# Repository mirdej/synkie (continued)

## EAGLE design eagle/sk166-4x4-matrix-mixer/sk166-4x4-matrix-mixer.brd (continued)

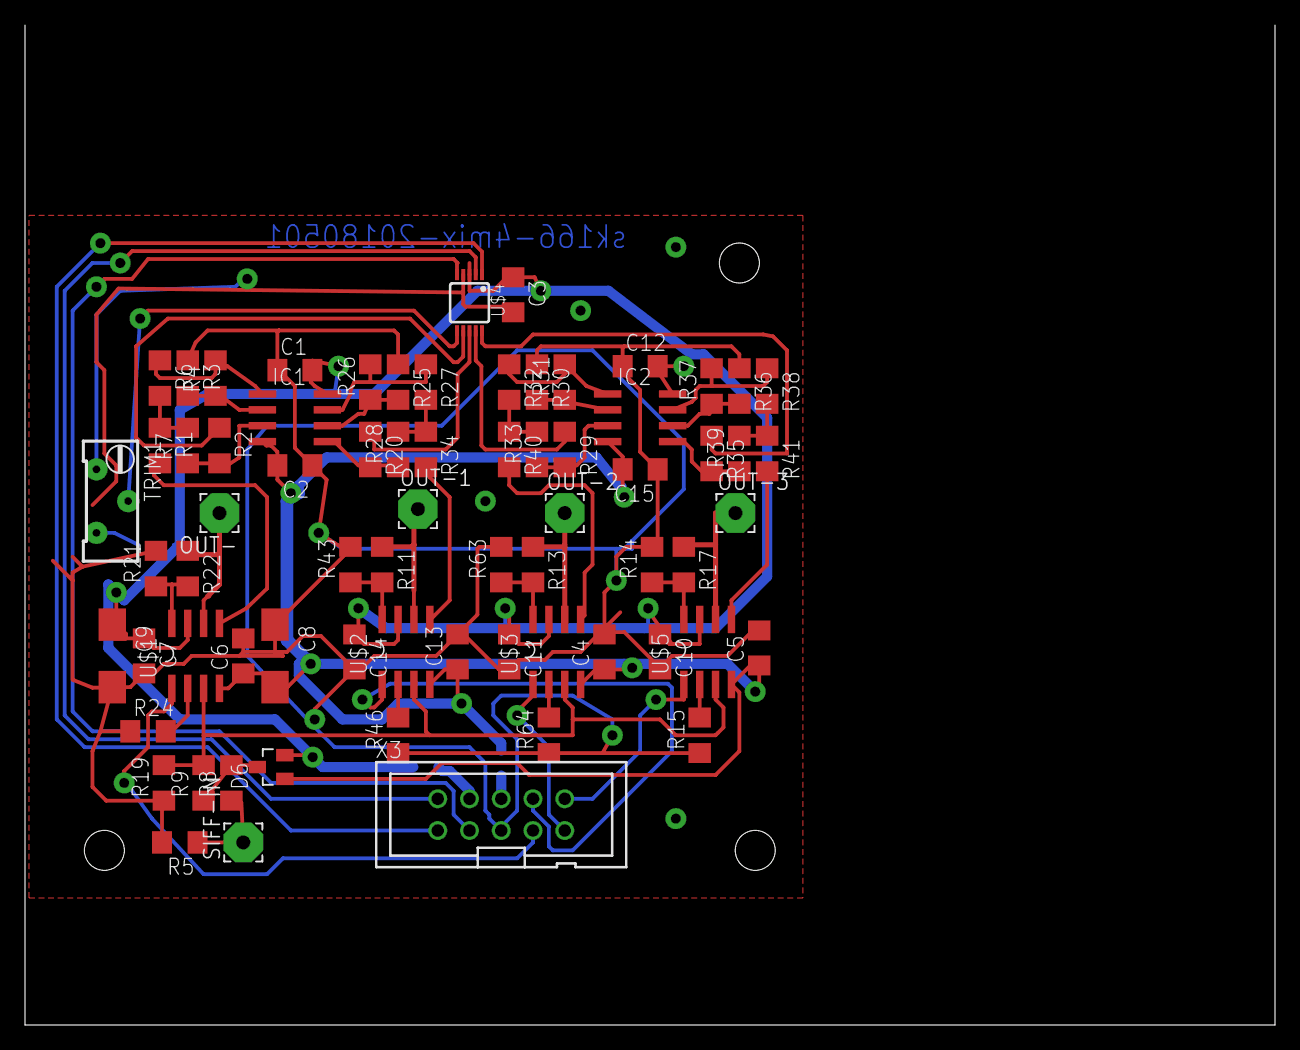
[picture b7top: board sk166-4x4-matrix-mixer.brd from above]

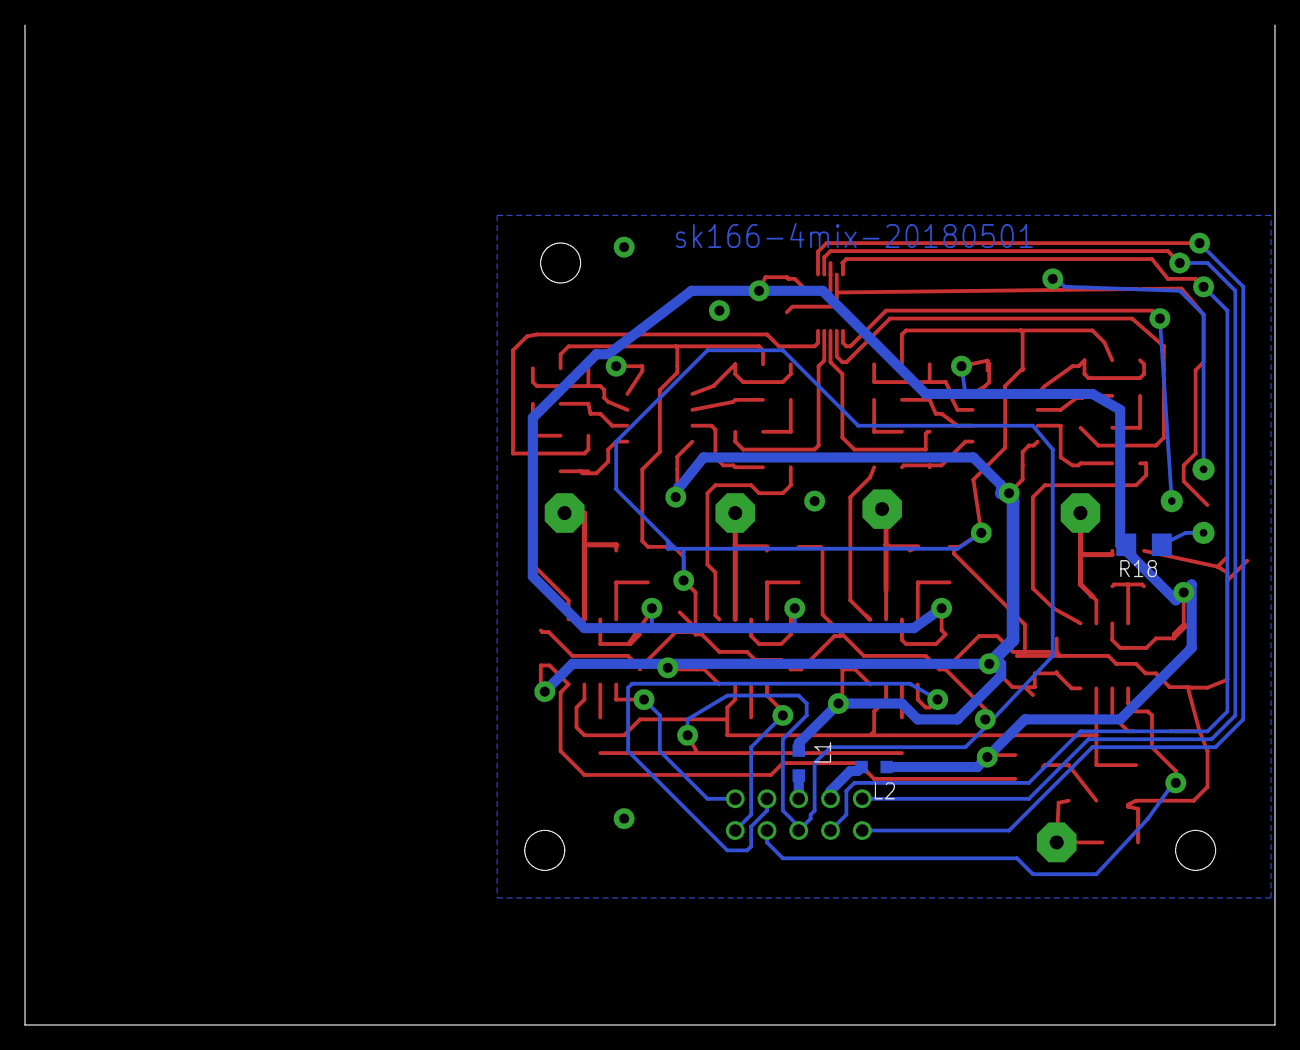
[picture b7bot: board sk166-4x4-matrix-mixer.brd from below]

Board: 2 copper layers, 100.0 x 80.0 mm, 73 parts (3 on the bottom side), 53 nets.

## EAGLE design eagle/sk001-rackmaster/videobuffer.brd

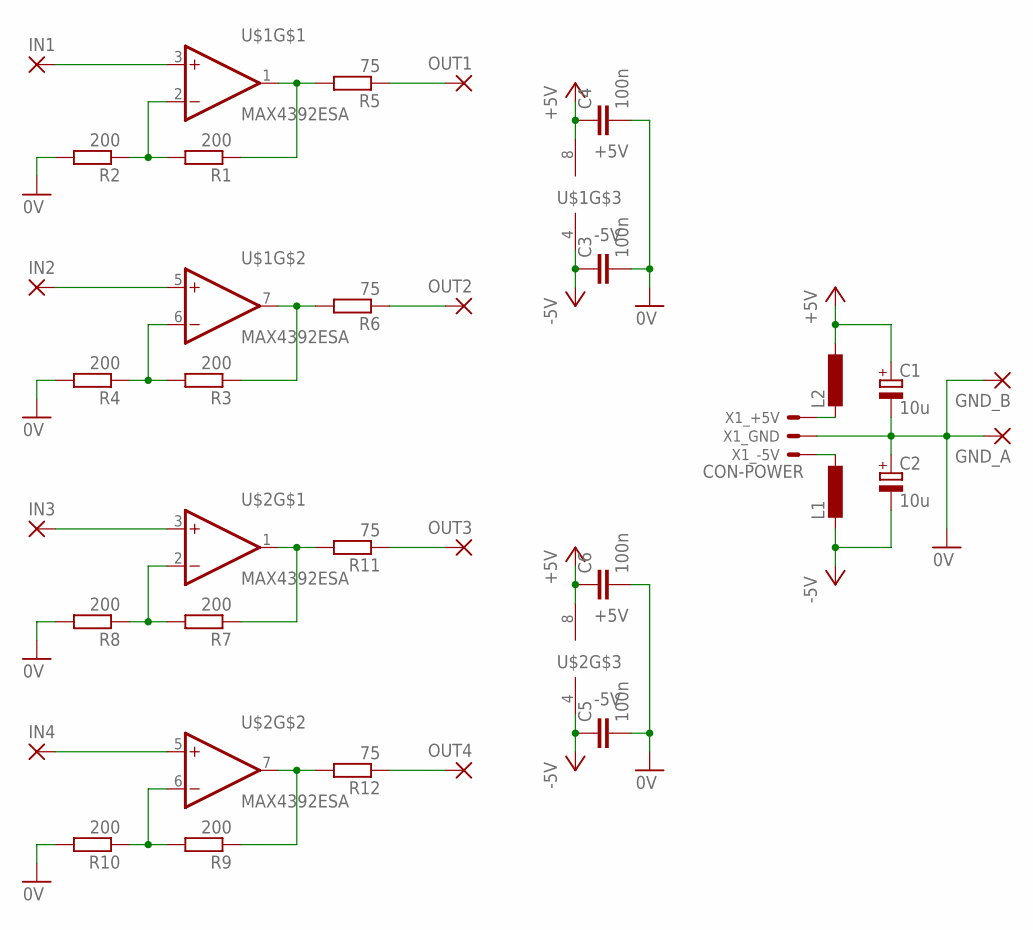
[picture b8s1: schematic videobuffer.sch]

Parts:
C1, C2: 10u; CT3528
C3, C4, C5, C6: 100n; C0805
GND_A: 3,17/1,1
GND_B: 3,17/1,1
IN1, IN2, IN3, IN4: 3,17/1,1
L1, L2: L-EU; L2012C
OUT1, OUT2, OUT3, OUT4: 3,17/1,1
R1, R2, R3, R4, R7, R8, R9, R10: 200; R0805
R5, R6, R11, R12: 75; R0805
U$1, U$2: MAX4392ESA; SO08
X1: CON-POWER; 22-23-2031

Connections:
0V: C1.-, C2.+, C3.2, C4.2, C5.2, C6.2, GND_A.1, GND_B.1, R2.2, R4.2, R8.2, R10.2, X1.2
+5V: C1.+, C4.1, C6.1, L2.1, U$1.8 (+5V), U$2.8 (+5V)
-5V: C2.-, C3.1, C5.1, L1.2, U$1.4 (-5V), U$2.4 (-5V)
unnamed: L1.1, X1.1
unnamed: L2.2, X1.3
unnamed: IN1.1, U$1.3 (+IN)
unnamed: IN2.1, U$1.5 (+IN)
unnamed: R3.2, R4.1, U$1.6 (-IN)
unnamed: R1.2, R2.1, U$1.2 (-IN)
unnamed: R1.1, R5.2, U$1.1 (OUT)
unnamed: OUT1.1, R5.1
unnamed: R3.1, R6.2, U$1.7 (OUT)
unnamed: OUT2.1, R6.1
unnamed: IN3.1, U$2.3 (+IN)
unnamed: IN4.1, U$2.5 (+IN)
unnamed: R9.2, R10.1, U$2.6 (-IN)
unnamed: R7.2, R8.1, U$2.2 (-IN)
unnamed: R7.1, R11.2, U$2.1 (OUT)
unnamed: OUT3.1, R11.1
unnamed: R9.1, R12.2, U$2.7 (OUT)
unnamed: OUT4.1, R12.1

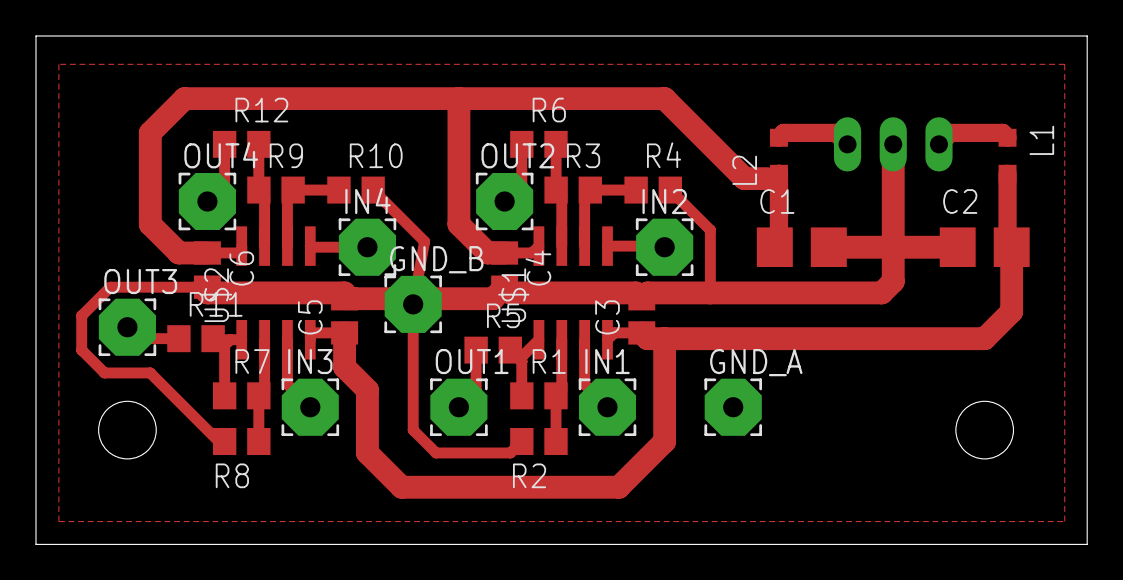
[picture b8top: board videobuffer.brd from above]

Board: 2 copper layers, 58.4 x 28.2 mm, 33 parts (1 on the bottom side), 21 nets.

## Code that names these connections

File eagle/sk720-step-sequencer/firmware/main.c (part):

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

	//PORTB:  ODD/even input, SPI
	DDRB 	= (1 << PB5) |(1 << PB2) | (1 << PB1);	// PB1: Neopixels, PB2: Latch for buttonsPB5 SCK
	PORTB 	= (1 << PC0);	//pull up sync in??
	SPCR 	= (1<<SPE)|(1<<MSTR)|(1<<SPR1)|(0<<SPR0); 		//  enable SPI in Master Mode, clk = fcpu/64 
	//PORTC
	DDRC 	= (1 << PC2) | (1 << PC1) | (1 << PC0); 		// Address Output
	PORTC 	= (1 << PC5) ; 						// pullup for in-sync input


	//PORTD:	Muxes
	DDRD 	= 0xff;
	// ------------------		Pin change Interrupts:
	// Trigger on PC3 = PCINT11
	// Reset on PC4 = PCINT12	
	// Odd/EVEN on PB0 = PCINT0
	PCICR 	= (1 << PCIE1) | (1 << PCIE0);
	PCMSK1 	= (1 << PCINT12) |(1 << PCINT11);
	PCMSK0  = (1 << PCINT0);
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	// check switches
	if (trigger_inhibit > 0) trigger_inhibit--;
	
	insync = PINC & (1 << PC5);
	
	// check buttons
	checkSPI();
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
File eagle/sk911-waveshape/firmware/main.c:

//---------------------------------------------------------------------------------------------
//	SK910	Waveshaper										ATMEGA88
//
//	Sample one vertical "line" of video as a wave and play it back at any frequency
//
// 	Part of the Synkie Project: www.synkie.net
//
// 	© 2017 Michael Egger, Licensed under GNU GPLv3
//
//--------------------------------------------------------------------------------------------
// ==============================================================================
// includes
// ------------------------------------------------------------------------------
// AVR Libc (see http://www.nongnu.org/avr-libc/)
#include <avr/io.h>			// include I/O definitions (port names, pin names, etc)
#include <avr/wdt.h>		// include watchdog timer support
#include <avr/interrupt.h>	// include interrupt support

// ==============================================================================
// Globals
// ------------------------------------------------------------------------------

unsigned int line_idx;
unsigned char x_pos;

// default sine wave, so you can use this module as a sine oscillator by tying PB3 to ground....
unsigned char table[256] = {0x80,0x83,0x86,0x89,0x8c,0x8f,0x92,0x95,0x98,0x9b,0x9e,0xa2,0xa5,0xa7,0xaa,0xad,0xb0,0xb3,0xb6,0xb9,0xbc,0xbe,0xc1,0xc4,0xc6,0xc9,0xcb,0xce,0xd0,0xd3,0xd5,0xd7,0xda,0xdc,0xde,0xe0,0xe2,0xe4,0xe6,0xe8,0xea,0xeb,0xed,0xee,0xf0,0xf1,0xf3,0xf4,0xf5,0xf6,0xf8,0xf9,0xfa,0xfa,0xfb,0xfc,0xfd,0xfd,0xfe,0xfe,0xfe,0xff,0xff,0xff,0xff,0xff,0xff,0xff,0xfe,0xfe,0xfe,0xfd,0xfd,0xfc,0xfb,0xfa,0xfa,0xf9,0xf8,0xf6,0xf5,0xf4,0xf3,0xf1,0xf0,0xee,0xed,0xeb,0xea,0xe8,0xe6,0xe4,0xe2,0xe0,0xde,0xdc,0xda,0xd7,0xd5,0xd3,0xd0,0xce,0xcb,0xc9,0xc6,0xc4,0xc1,0xbe,0xbc,0xb9,0xb6,0xb3,0xb0,0xad,0xaa,0xa7,0xa5,0xa2,0x9e,0x9b,0x98,0x95,0x92,0x8f,0x8c,0x89,0x86,0x83,0x80,0x7c,0x79,0x76,0x73,0x70,0x6d,0x6a,0x67,0x64,0x61,0x5d,0x5a,0x58,0x55,0x52,0x4f,0x4c,0x49,0x46,0x43,0x41,0x3e,0x3b,0x39,0x36,0x34,0x31,0x2f,0x2c,0x2a,0x28,0x25,0x23,0x21,0x1f,0x1d,0x1b,0x19,0x17,0x15,0x14,0x12,0x11,0xf,0xe,0xc,0xb,0xa,0x9,0x7,0x6,0x5,0x5,0x4,0x3,0x2,0x2,0x1,0x1,0x1,0x0,0x0,0x0,0x0,0x0,0x0,0x0,0x1,0x1,0x1,0x2,0x2,0x3,0x4,0x5,0x5,0x6,0x7,0x9,0xa,0xb,0xc,0xe,0xf,0x11,0x12,0x14,0x15,0x17,0x19,0x1b,0x1d,0x1f,0x21,0x23,0x25,0x28,0x2a,0x2c,0x2f,0x31,0x34,0x36,0x39,0x3b,0x3e,0x41,0x43,0x46,0x49,0x4c,0x4f,0x52,0x55,0x58,0x5a,0x5d,0x61,0x64,0x67,0x6a,0x6d,0x70,0x73,0x76,0x79,0x7c};
unsigned char table_read_idx;
unsigned char do_sample_video;
unsigned int cv_input;

unsigned char fast_mode;
unsigned char ramp_input;


// ==============================================================================
// Functions
// ------------------------------------------------------------------------------



// ------------------------------------------------------------------------------
// Init
// ------------------------------------------------------------------------------
void init (void) {
	DDRB = (1 < PB1);		//Osc_Out
	DDRC = (1 << PC4); 		//pulse out
	DDRD = 0xFF; // R2R Ladder DAC
	
	PORTC |= (1 << PC3); 	// pullup for fast/slow, switch
	PORTB |= (1 << PB3); 	// pullup for rec switch
	PORTB |= (1 << PB0);	// pullup for osc/ramp, switch
	
	
	
	// Pin change Interrupts
	// HSYNC on 		PC5 = PCINT13
	// Odd/EVEN on 		PB2 = PCINT2
	PCICR 	= (1 << PCIE1) | (1 << PCIE0);
	PCMSK1 	= (1 << PCINT13);
	PCMSK0  = (1 << PCINT2);		// PB2 - O/E
	
	// Timer 0 : H-Sync Pulse Delay max 64us  @ 20Mhz = 1280 Clock Cycles
	//												Prescaler 8 -> OCR0 0-160 (better something like 10-150...?)
	set_x_pos(50);
	TCCR0A = 0; 				// Normal mode, no OC= pins connected
	TIMSK0 = ( 1 << OCIE0A);	// Output compare interrupt enabled
								// Timer still stopped
	
	
	// ------------------		ADC
	//"By default, the successive approximation circuitry requires an input clock frequency between 50kHz and 200kHz to get maximum resolution"
	// "A normal conversion takes 13 ADC clock cycles. The first conversion after the ADC is switched "
	// Max 200kHz @ 20 MHz -> >1700 clk cycles... to slow for 16khz sampling
	
	ADCSRA 	= (1 << ADEN | 1 << ADATE | 1 << ADIE);						// Enable ADC
	ADCSRA |= (1 << ADPS2) | (1 << ADPS1);								// prescaler 64
	ADMUX = (1 << ADLAR);												// we're only reading 8bits, so left adjust result
	ADCSRB	= (1 << ADTS1) | (1 << ADTS0);								// Trigger ADC on Timer 0 COMPA
	ADCSRA |= (1 << ADSC);												// Start Conversion
	
	// Timer 1 : speed of reading back samples -> output frequency
	// 
	OCR1AL = 0xdf;
	TCCR1A = ( 1 << COM1A0 );						// Toggle OC1A on compare match, 
	TCCR1B = ( 1 << WGM12 | 1 << CS10);				// CTC Mode, no prescaler @20mhz / 256 -> max 78.125khz sampling rate
	TIMSK1 = (1 << OCIE1A); 

	wdt_enable(WDTO_30MS);			// enable watchdog timer
	sei();
}




// ------------------------------------------------------------------------------
// 													odd/even - vertical blanking
// 											on one field sample cv, on other video
ISR (PCINT0_vect) {  						
	line_idx = 0;
	if (PINB & (1 << PB2)) {
		if (PINB & (1 << PB3))	{			// field 1
			do_sample_video = 1;
			ADCSRA |= (1 << ADPS2) | (1 << ADPS1);								// prescaler 64
			ADMUX = (1 << ADLAR);												// adc0				= VIDEO 
		}
	} else {
		ADCSRA |= (1 << ADPS2) | (1 << ADPS1) | (1 << ADPS1);								// prescaler 128 for 10bit resolution

		ADMUX = (1 << ADLAR) | 1;			// adc 1 = CV
		do_sample_video = 0;
	}
	
	if (PINC & (1 << PC3)) {	
		fast_mode = 1;
	} else {
		fast_mode = 0;
	}
	
	if (PINB & (1 << PB0)) {	
		ramp_input = 0;
		TCCR1B |= (1 << CS10);				// run with no prescaler
	} else {
		ramp_input = 1;
		TCCR1B &= ~(1 << CS10);				//stop timer		
	} 
}

// ------------------------------------------------------------------------------
// 														H-Sync

ISR (PCINT1_vect) {
	// Start Timer -> Pulse delay
if ( PINC & (1 << PC5)) {
	TCNT0 = 0;
		OCR0A 	= x_pos;
		TCCR0B |= ( 1 << CS01 );		// clk/8 prescaler -> start timer
		line_idx++;
	}
}  

// ------------------------------------------------------------------------------
// 														Pulse Start
ISR (TIMER0_COMPA_vect) {
	PORTC |= (1 << 4);	 //Pulse High
	TCCR0B &= ~( 1 << CS01 );		// stop timer  - adc is started automatically by interrupt
}

void set_x_pos(unsigned char n) {
	if (n < 10) x_pos = 10;
	else if (n > 130) x_pos = 130;
	else x_pos = n;
}
// ------------------------------------------------------------------------------
// 														ADC complete interrupt

ISR (ADC_vect) {
	PORTC &= ~(1 << 4);					//stop pulseout
	if (do_sample_video) {
		if (line_idx > 35) {
			if (line_idx < 292) {
				table[line_idx - 36] = ADCH;
			}
		}
	} else {
		if (line_idx == 50) {
			if (ramp_input) {
				cv_input = ADCH;
				PORTD = table[cv_input];
			} else {
				cv_input = (ADCL | ADCH << 2);				// Left adjusted ADC result
				cv_input = 1024 - cv_input;
			
			
				if (!fast_mode) {
					cv_input *= 16;				
				}
				// keep minimum 20 clks -> 1MHZ overflow / 256 Table size -> 3.9kHz fastest
				if (cv_input < 100) OCR1A = 100;
				else OCR1A = cv_input;
			}
			
			ADCSRA |= (1 << ADPS2) | (1 << ADPS1);								// prescaler 64
			ADMUX = (1 << ADLAR) | 2;												// adc02
				

		} else if (line_idx == 120) {
			cv_input = ADCH;
			cv_input /= 2;
			if (cv_input > 1) {						// only if there seems to be signal
				set_x_pos(cv_input);
			} else {
				set_x_pos(50);
			}
			ADCSRA |= (1 << ADPS2) | (1 << ADPS1);								// prescaler 64
			ADMUX = (1 << ADLAR) ;												// adc0
		}
	}
}

// ------------------------------------------------------------------------------
// 														Timer 1 Overflow: output next sample

ISR (TIMER1_COMPA_vect) {
	PORTD = table[table_read_idx++];
} 


// ==============================================================================
// main
// ------------------------------------------------------------------------------

int main (void) {

	
	init();

	while(1) {
		wdt_reset();		
	}
	return 0;
}	

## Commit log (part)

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2013-11-23 another take on the master time module
2013-11-23 now with audio click track support.
2013-11-23 audio input board with envelope replaces ac coupling and biasing on sk556-time board
2013-11-23 supply of ramp out opamp was wrong way round
2013-11-23 first version of cv-looped-motor control
2013-11-23 half-hearted attempt to make this stuff synchronisable by beat interrupt. will move to ramp synchronized approach
2013-11-24 one channel woring
2013-11-26 main.c appartently got corrupted by bad copy-paste jobs for other modules. reverted back to revision 104
2013-12-09 added second version of ramps module
2013-12-10 corrected r and c values
2013-12-29 improved gain by ting R215 to base of bias pot. reduced oscillation with bigger r307/r308
2013-12-29 added first version of sk800
2013-12-30 second version of subcarrier module. untested
2014-05-26 added sk010-refgen
2014-05-26 added board
2014-05-28 added firmware
2014-05-28 re-wrote firmware in assembler
2014-05-29 added generation of sync bus signals*
2014-05-31 second prototype and follow-up corrections
2014-08-08 added smoothing
2014-10-13 added very old audio-cv module from 2012
2014-10-13 added newly routed aux in module using triple digit naming scheme
2014-10-13 adapted disasm target for using build folder
2014-10-13 better board layout
2014-10-14 added offset pot, routed board
2014-10-14 added frontplate
2014-10-14 added note about pot pad sizes
2014-10-14 added sk590-audio-inject
2014-12-29 added missing connection and capacitor, finished routing
2014-12-30 reimplemented audio click detection
2015-05-24 added subcarrier oscillator study
2015-05-24 updated values, small fixes
2016-01-03 Migrating wiki contents from Google Code
2016-01-04 corrected date on pcb
2016-01-05 changed footprint of transfo, added 100p anti-oscillation capas
2016-01-06 fixed power supply connector was reversed
2016-01-08 added .gitignore
2016-01-08 added second version of subcarrier proto, and synkie eagle lib
2016-01-08 added comment about values on paper schema
2016-02-06 moved sync connector ôut of way of banana plug
2016-05-07 added mcugen
2016-05-07 removed lock files
2017-05-29 added rackmaster
2017-06-06 add vga breakout and multiple
2017-06-06 clean up silk layers for production
2017-08-04 only listen to every other color burst because of alternating phase
2017-08-04 add new modules
2017-10-14 add sk242 chroma
2017-10-27 first version of untested firmware
2017-11-06 version1 of stepsequencer
2017-11-06 forgot file
2018-03-19 michis mods
2018-03-19 add spectrum analyzer
2018-03-19 add eqs
2018-03-19 add clipper
2018-03-20 added .lck files to gitignore
2018-03-20 sk181-clipper: replaced buffer op amps and diodes with transistors
2018-03-22 fixed(?) ramp input
2018-03-22 sk001: new clipper with transistors
2018-03-22 add phgaseshift
2018-03-23 scabi with logarithmic gain control
2018-03-23 named signals
2018-03-23 add 4x4 matrix mixer
2018-03-24 scabi-log scale: sum before exponentiating
2018-05-01 less capacity on output. no resistor
2018-05-02 added videobuffer
2018-05-03 sorted out pot order
2018-05-11 increased matrix mixer feedback resistances to avoid ringing
2018-09-09 rackmaster: added lowpass to lm1881 input
2018-09-09 mcugen: added pull-downs for outputs, switched supply pins on programming connector
2018-10-06 routed remaining air wire
2018-10-10 correct date
2018-10-22 add frontplate
2018-10-30 correct resistor values)
2018-11-02 first levelmeter
2019-05-28 add new kicad modules
2019-06-02 added allpass and bwlim experiments
2019-11-11 various
2019-11-12 ported sk108-scabi-log to kicad
2019-11-12 addedd kicad template for synkie modules
2019-11-12 modified BAT54S symbol to remove weird pin standing out
2019-11-12 added default power and signal in sections to synkie module template
2019-11-12 added some kicad temporary files to .gitignore
2019-11-12 changed PEMX1 symbol to have pin names outside
2019-11-14 added sk161-modular-mixer; NOTE: board needs to be corrected to adapt to corrected slider pot footprint!
2019-11-14 added conn 1x10 to synkie_symbols
2019-11-14 fixed symbols / footprints references in sk034-allpass
2019-11-15 added footprint and maximum module board size to template
2019-11-15 added new modular mixer master board
2019-11-15 updated values for better image
2019-11-15 minimized some bare zones
2019-11-15 change footfrints
2019-11-15 corrected footprint of ferrite beads
2019-11-15 added modular mixer channel board
2019-11-15 new values
2019-11-15 added obsolescence note for old 'sk161-modular-mixer.pro' project
2019-11-16 updated LT1228 symbol
2019-11-18 mixer modules ready for fabrication. allpass with dual-pot
2019-11-18 change to 2pin connectors for sync signal
2019-12-08 modular mixer: updated values for better gain ranges
2019-12-09 new scabi-log with transistors for U->I conversion
2020-08-13 modular mixer for fabrication
2020-08-18 added PMBT3906YS dual PNP symbol and footprint
2020-08-19 increased pad size of SOT-666 footprint for easier etching/soldering
2020-08-19 added diode symbol to library
2020-08-19 added new clipper with automatic levels
2020-08-19 add new sync splitter
2020-08-19 add new resyncer
2020-08-20 Better black level for clipper
2020-08-20 fixed symbols for PMBT3906 were referencing rescue library
2020-08-20 .gitignore
2020-08-20 added LM311 to synkie_symbols
2020-08-21 prepare microsynkie for fabrication
2020-08-21 updated synkie_symbols.bck
2020-08-21 add atmega88 symbol
2020-08-21 add dac
2020-08-25 smaller switch footprint
2020-08-27 add symbols
2020-08-27 add footprints
2020-08-27 add sk720 schematic
2020-08-28 ready for fab
2020-09-04 change footprints C to 0603
2020-09-14 add firmare. change 1206 footprints to 0805
2020-09-14 add laser files
2020-09-19 add sk730
2020-09-28 change globals to valatile to prevent crashes. make version for pragramming throuigh Arduino IDE
2020-10-15 added footprint of uwe pots to library
2020-10-16 added sk508-chua
2020-10-18 first version 4fach compa mit fix levels für die stufen 0-1V
2020-12-13 4 layer versions. scabi with levelmeter
2020-12-24 c footprints
2020-12-25 better color frequency response
2020-12-26 module template: changed default input resistor values
2020-12-26 added LM339 to synkie library
2020-12-26 added sk221-compa-edges
2021-01-03 power supply protection diodes
2021-01-06 add anyma logo
2021-01-13 write steps to eeprom
2021-01-14 wait 30secs before writing eeprom in order to limit number of succesive writes
2021-05-15 added gyrator-based equalizer experiment
2021-05-15 added footprint for big smd elcos to synkie_footprints
2021-05-15 added trigger regularizer
2021-05-15 increased trigreg output pulse length
2021-09-06 add filters from circuitcontrol drersden
2021-09-06 add sk light/cv modules
2021-09-13 note on moog
2021-09-24 new resyncer based on anymix21 output. simply named sk003-output from now on
2021-09-24 add genlock in module. this is the new sync-splitter
2021-09-24 rename with right prefix
2021-09-24 fix sheet link
2021-09-29 correct polarity
2021-10-02 correct pot polarity
2021-10-15 oscra changes
2021-10-15 update kicad libraries
2021-10-16 add new input clamp
2021-10-17 add handmade sk006-version
2021-10-23 add pal notice
2021-10-23 version with dual-trans and INA
2021-10-23 add new tourbox
2021-10-23 first version of subcarrier module
2021-10-24 add simplified version (not fully tested)
2021-10-31 add multiple
2021-10-31 add missing 75Ohm termination on input
2021-11-02 add missing jtag vzarget
2021-11-11 add documentation
2021-11-11 cosmetics
2021-11-14 delay does not work. will change to fpga
2021-11-23 add missing pulldown. change r1206 to 0805
2021-12-03 add vcos
2021-12-04 correct footprints. more gain on subcarrier
2021-12-21 add power distro
2021-12-21 burstphase
2021-12-21 add matrix
2021-12-21 rgb module
2021-12-21 add logo symbol
2021-12-21 sk108-scabi-log: fixed op amp inputs were reversed since 2020-12-13 (commit 16a4c41fa6f06a2b7dd2fa5efc88025a5135e06a)
2021-12-21 fixed a few typos in readme
2021-12-21 sk001-genlock-in: changed logo symbol to reference synkie_symbols
2021-12-21 added fp-lib-table and sym-lib-table to gitignore, fixed bom ignore
2021-12-21 added eagle-import files in eagle folder (generated by kicad) to gitignores
2021-12-22 missing capacitor
2021-12-27 change to sykiepad
2021-12-30 add umcc connector
2022-01-01 improve return paths in pcb. stacking order should be F,B,In2,In1
2022-01-20 change layer stackup
2023-01-18 add monitor resyncer
2023-01-31 add buffers for input and burst
2023-04-08 added sk509-noise
2024-08-26 sk502-vco-triple: removed bom
2024-08-26 sk509-noise: added comments on things to try on schema
2024-08-26 removed empty 0034-1496test
2024-08-26 update symbols
2024-08-27 add trigger guzzi
2024-08-27 updated sk509-noise for new experimental board; component values set so that circuit corresponds to previous prototype
2024-08-27 update to lateat state of prototype board
2024-08-27 updated schema to match final version; board needs re-routing!
2024-08-27 route for china
2024-08-27 add pulsedelay
2024-08-29 added sk504-ltvco
2024-08-29 added some more kicad-specific entries (*-backups/, *.kicad_prl) to .gitignores
2024-09-03 gitignore
2024-09-03 add frontplate part library
2024-09-03 add ne frontplate
2024-09-03 updated schema with values tuned for low-frequency vco; board outdate!
2024-09-03 migrate symbol library
2024-09-03 new kicad version. note on dc levels/genlock
2024-09-18 reroute pcb
2024-09-27 deleted autosave files
2024-09-27 delet autosave
2024-09-27 sk800: removed question marks from resistor values
2025-10-16 add handmade anaguzzi
2025-10-21 added sk162-herd-mixer
2025-10-21 removed lib-table files from .gitignores
2025-10-21 sk162: removed unnecessary pull-down on inputs, reannotated
2025-10-21 added kicad _autosave-* files to gitignores
2025-10-25 update footprints
2025-10-25 added sk162-herd-mixer single-board version schema
2025-10-25 silkscreen
2025-10-25 add inverter
2025-10-25 remove prod folder
2025-10-25 added 'production' folder to gitignore
2025-10-25 partially routed sk162
2025-10-26 more 3d models
2025-10-26 routed sk162
2025-10-27 add some vias on suply
2025-10-28 added switch SPDT to synkie_symbols
2025-10-29 added sk110-cvadd
2025-10-30 sk162: corrected value of output gain resistor
2025-10-30 sk110: fixed bias pot low connection, fixed oscillation on bias op-amp
2025-10-30 added 4053, mounting hole to synkie_symbols
2025-10-30 corrected pin name on 4053 symbol
2025-10-30 added kicad .bak files to gitignores
2025-11-01 added MC1496 to synkie_symbols
2025-11-02 routed sk110-cvadd
2025-11-23 add crocodile pad
2025-11-24 sk162: updated schema according to first prototype: adapted output gain to 470/220, fixed termination of unused CFAs
2025-11-24 updated pcb for schema fixes
2025-11-24 added croco hole
2025-11-25 add sk801
2025-11-25 sk110: added croco hole, fixed: cfa termination, power connector orientation
2026-02-17 footprints
2026-02-17 new audio2cv, not routed yet
2026-02-18 layout
2026-02-19 add lfo
2026-02-19 add AI frequency propositions
2026-02-20 v9 schematic
2026-02-20 add new renamed sk001 with better subcarrier
2026-02-20 remove old sk001
2026-02-20 input buffert
2026-02-20 ac couple sc
2026-03-18 corrections
2026-03-23 new modules
2026-03-23 more changes
2026-03-23 more
2026-03-23 jlc version
2026-03-23 add ramps
2026-03-23 new bus, frontplates
2026-03-26 add module
2026-03-26 fix pot direction, schottkys
2026-03-26 more footprints
2026-03-26 new module
2026-03-26 fix poti direction, supply
2026-03-27 new output
2026-03-27 jlc order
2026-03-29 dd module
2026-03-29 production
2026-04-02 fix silkscreen, polarity
2026-04-14 fix outputs, silk
2026-04-15 fix r values
2026-05-13 fix output resistors, footprints, add picoblade
2026-05-15 cleanup
2026-05-15 add sk128
2026-05-15 remove old templates, add buiöding blocks
2026-05-15 add building blocks
2026-05-15 verticals, more designblocks
2026-05-15 ne5532 version
2026-05-15 add pms,pmm
2026-05-16 footprints and designblocks
2026-05-16 cleanup before redesign
2026-05-16 simpler version, new bus
2026-05-17 rgb module ad724 w hard clippers
2026-05-17 cheap clip?
2026-05-17 change big bus to 16 pins
2026-05-17 new version
2026-05-17 new bus connector
2026-06-01 buffered output 1V, 0.1V Hysteresis
